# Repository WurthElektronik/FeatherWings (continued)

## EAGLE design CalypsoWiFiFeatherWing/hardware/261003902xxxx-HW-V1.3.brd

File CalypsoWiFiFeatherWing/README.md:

# Calypso Wi-Fi FeatherWing

## Introduction

The Würth Elektronik eiSos [Calypso Wi-Fi FeatherWing](https://www.we-online.de/katalog/en/CALYPSO_FeatherWing) is a development board that offers a secure 2.4 GHz Wi-Fi connectivity solution. It is fully compatible to the popular [Adafruit](https://www.adafruit.com/) [Feather line](https://www.adafruit.com/feather) of development boards and extends the Feathers with Wi-Fi connectivity.

The Calypso Wi-Fi FeatherWing consists of the [Calypso radio module](https://www.we-online.com/catalog/en/CALYPSO) that offers Wi-Fi connectivity based on **IEEE 802.11 b/g/n** with a fully featured TCP/IP stack. With out-of-the-box support to commonly used network applications like **SNTP**, **HTTP(S)**, **MQTT(S)**, Calypso offers easy and secure solutions to any **IoT application**.

It has an AT-style command interface on the standard UART and hence can be connected to any of the Feather microcontroller boards. The [Arduino](https://www.arduino.cc/) (C/C++) drivers and examples made available makes it easy to build a prototype to kick-start the application development.

This repository contains the [Eagle](https://www.autodesk.com/products/eagle/overview) design files for the Calypso Wi-Fi FeatherWing [PCB](hardware) as well as the [software](software) with quick start example.

For more information, please download the [Calypso Wi-Fi FeatherWing user manual](docs/CalypsoFeatherWing.pdf). Feel free to check our [YouTube channel](https://www.youtube.com/user/WuerthElektronik/videos) for video tutorials, hands-ons and webinars relating to our products.

## Hardware

### Description

The Calypso Wi-Fi FeatherWing was designed with rapid prototyping in mind. Being fully compatible with the Adafruit ecosystem, this FeatherWing gives the user the flexibility to choose the preferred host microcontroller. The inherent modularity of the ecosystem allows the FeatherWing to be easily integrated into any project.

### [Calypso Wi-Fi module](https://www.we-online.com/catalog/en/CALYPSO) [(2610011025000)](https://www.we-online.de/katalog/datasheet/2610011025000.pdf)

The Calypso Wi-Fi module is a compact Wi-Fi radio module based on IEEE 802.11 b/g/n with a fully featured TCP/IP stack. The edge castellated connections, smart antenna configuration and an easy-to-use AT-style command interface enable easy integration of the Calypso into any embedded application.

The module supports IPv4 as well as IPv6 and implements several commonly used network applications like SNTP, DHPv4, DHCPv6, mDNS, HTTP(S), MQTT(Secure) out-of the box. Advanced security features like up to 6 simultaneous secure sockets, secure boot, secure storage and secure OTA update provide a good basis for a secure end product.

Whether a serial cable replacement or low power IoT application with cloud connectivity, the Calypso Wi-Fi modules offers a robust and standard compliant wireless connectivity solution for low-power and low-medium throughput applications.

### Key features

Calypso offers the user to configure and exploit its rich features through an easy-to-use command interface over UART.

| Feature | Description |
| ------- | ----------- |
| Radio standards | IEEE 802.11 b/g/n station <br>IEEE 802.11 b/g Access point (for provisioning only)<br> Wi-Fi Direct client and group owner |
| Channels | 1-13 |
| Security | WEP, WPA/WPA2PSK, WPA2 Enterprise (802.1x) |
| Provisioning | In AP mode using the on-board HTTPS server |
| Network layer | IPv4, IPv6 |
| IP addresssing | Static, LLA, DHCPv4, DHCPv6 with DAD 
| Transport layer | TCP, UDP<br>SSLv3.0/TLSv1.0/TLSv1.1/TLSv1.2<br>Up to 15 simultaneous sockets of which 6 can be secure |
| Network applications | MQTT(Secure) client<br>HTTP(S) client<br>SNTP client<br>HTTP(S) server<br>mDNS, DNS-SD<br>DHCP server<br> Ping |
| Update | Secure OTA update with fall back mechanism |
| Security | Secure key storage<br>Trusted root-certificate catalog<br>Encrypted file system<br>Secure OTA<br>Software tamper detection<br>Cloning protection |
| Power management | 802.11 power save power modes <br>Lower power sleep mode with timed or pin wake-up |

### Pinouts 

#### Feather Connector
This is the standard set of connectors that is used across the Feather ecosystem. The table below describes the functions of each of the 28 pins as applicable to this FeatherWing.

| Pin number | Pin name | Function |
| ------- | ------- |----------------|
|    1          | <span style="text-decoration:overline">RST</span> | Not connected|
|    2          | 3V3| 3.3V power supply|
|    3          | AREF| Not connected|
|   4          | GND| Ground|
|    5          | A0| Not connected|
|    6          | A1| (Optional) Calypso APP_MODE_0 pin via JP3|
|    7          | A2| (Optional) Calypso APP_MODE_1 pin via JP3|
|    8          | A3| Not connected|
|    9          | A4| Not connected|
|    10         | A5| Not connected|
|    11         | SCK| Not connected|
|    12         | MOSI| Not connected|
|    13         | MISO| Not connected|
|    14         | U0RX| Calypso UTXD pin|
|    15         | U0TX| Calypso URXD Pin|
|    16         | NC| Not connected|

| Pin number | Pin name | Function |
| ------- | ------- |----------------|
|    17         | SDA| Not connected|
|    18         | SCL| Not connected|
|    19         | 5| Not connected|
|    20         | 6| (Optional) Calypso WAKE_UP pin via JP3|
|    21         | 9| Not connected|
|    22         | U1TX| Not connected|
|    23         | U1RX| Not connected|
|    24         | 12| (Optional) Switch S2 via JP3|
|    25         | 13| Not connected|
|    26         | 5V| Not connected|
|    27         | EN| Not connected|
|    28         | VBAT| Not connected|   

#### Jumper JP2
This jumper enables the user to start Calypso Wi-Fi module in different modes through the APP_MODE_0 and APP_MODE_1 pins. 

| Pin connection | Function  | Jumper set (Default) |
| ------- | ------- |----------------|
|    1,3	| APP_MODE_0 to HIGH |	No |
|    3,5	|APP_MODE_0 to LOW |	No |
|    2,4	| APP_MODE_1 to HIGH |	No |
|    4,6	|APP_MODE_1 to LOW |	No |

The table below briefly describes the different application modes of Calypso. Please refer to Section 5.2 of the Calypso [user manual](https://www.we-online.com/catalog/manual/2610011025000_Calypso%20261001102500x%20Manual_rev1.pdf) for further details. For normal operation in the standard AT-command mode, these jumpers do not need to be mounted as the lines are pulled down internally.

| APP_MODE_0 | APP_MODE_1  | Mode |
| ------- | ------- |----------------|
|    0	| 0  |	AT command normal mode |
|    0	|1 |	FOTA update mode |
|    1	| 0 |	Provisioning mode |
|    1	|1 |	AT command terminal mode |

#### Jumper JP3
This jumper allows the connection of Calypso pins APP_MODE_0, APP_MODE_1, WAKE_UP to the host microcontroller. Additionally, it allows the general purpose switch S2 to be connected to GPIO 12.

| Pin connection | Function  | Jumper set (Default) |
| ------- | ------- |----------------|
|    1,2|	S2 to GPIO12|	Yes|
|    3,4|	APP_MODE_0 to GPIOA1|	No|
|    5,6|	APP_MODE_1 to GPIOA2|	No|
|    7,8|	WAKE_UP to GPIO6|	No|

#### Push button S1
This push button is connected to the /RESET pin of the Calypso Wi-Fi module. Pressing this button resets the module.

#### Push button S2
S2 is a general purpose push button which is connected to GPIO 12 when a jumper is set between pins 1 and 2 of JP3. This switch can be used to trigger a specific action like switching the Calypso into provisioning mode.

### Schematics

### DISCLAIMER:
THE USE OF THE WÜRTH ELEKTRONIK EISOS DESIGN EXAMPLE / REFERENCE DESIGN IS ENTIRELY AT YOUR OWN RISK. IT IS YOUR SOLE RESPONSIBILITY TO IMPLEMENT THE DESIGN EXAMPLE / REFERENCE DESIGN WITH ALL TECHNICAL AND REGULATORY REQUIREMENTS IN YOUR APPLICATION. IT IS ALSO YOUR RESPONSIBILITY TO VERIFY THE FUNCTION AND PERFORMANCE OF YOUR DESIGN IN YOUR OWN PARTICULAR ENGINEERING AND PRODUCT ENVIRONMENT AND YOU ASSUME THE ENTIRE RISK OF DOING SO OR FAILING TO DO SO. THE WÜRTH ELEKTRONIK EISOS DESIGN EXAMPLE / REFERENCE DESIGN IS PROVIDED ON AN "AS IS" OR "AS AVAILABLE" BASIS, WITHOUT ANY WARRANTIES OF ANY KIND AND WÜRTH ELEKTRONIK EISOS DISCLAIMS ANY WARRANTIES EXPRESS OR IMPLIED, INCLUDING WITHOUT LIMITATION THE MERCHANTABILITY OR FITNESS FOR A PARTICULAR PURPOSE, USAGE OR THE NON-INFRINGEMENT OF THIRD PARTIES’ INTELLECTUAL PROPERTY RIGHTS. NO LICENSE IS GRANTED TO ANY INTELLECTUAL PROPERTY RIGHT BY WÜRTH ELEKTRONIK EISOS OR ANY THIRD PARY. UNDER NO CIRCUMSTANCES SHALL WÜRTH ELEKTRONIK EISOS BE LIABLE FOR DAMAGES INCURRED BY REASON OF OTHER SERVICES OR PRODUCTS RECEIVED THROUGH OR ADVERTISED IN CONNECTION WITH THE WÜRTH ELEKTRONIK EISOS SITE OR THE WÜRTH ELEKTRONIK EISOS DESIGN EXAMPLE / REFERENCE DESIGN. THE WÜRTH ELEKTRONIK EISOS DESIGN EXAMPLE / REFERENCE DESIGN IS SUBJECT TO CHANGE WITHOUT NOTICE.

## Software

A Calypso Wi-Fi FeatherWing quick start example can be found in the [software folder](software). Please check the [cloud connectivity folder](../Sensor2CloudConnectivity) for more examples for sensor to cloud solutions.

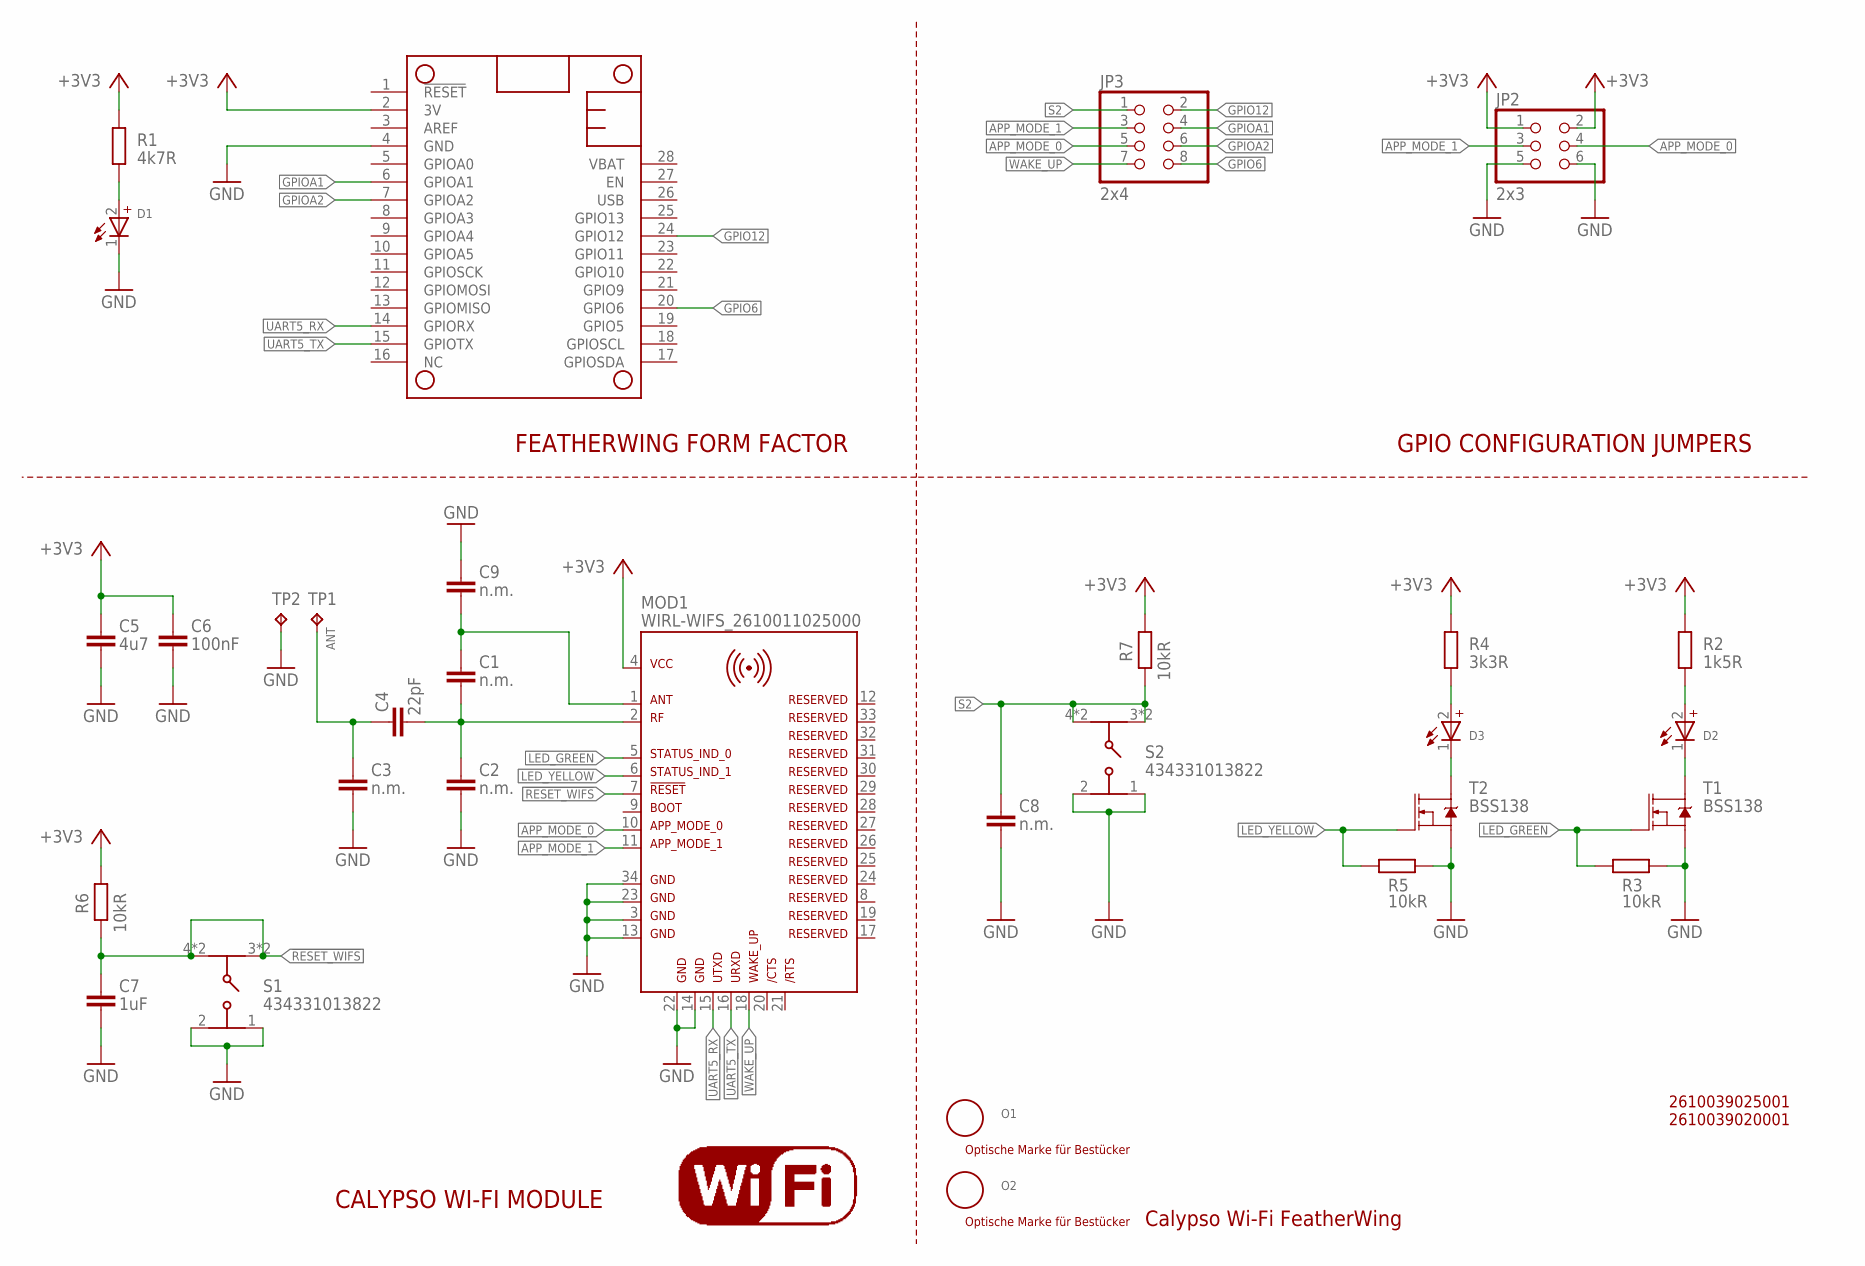
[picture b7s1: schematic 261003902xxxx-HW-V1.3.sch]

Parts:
C1, C8: n.m.; C0402_IPC
C2, C3, C9: n.m.; C0201_IPC
C4: 22pF; C0402_IPC
C5: 4u7; C0402_IPC
C6: 100nF; C0402_IPC
C7: 1uF; C0402_IPC
D1: RED; WL-SMSW_1204_A
D2: GREEN; WL-SMSW_1204_A
D3: YELLOW; WL-SMSW_1204_A
JP2: 2x3; 2X03
JP3: 2x4; 2X04
MOD1: WIRL-WIFS_2610011025000
MS1: header: 1 x 12 & 1 x 16; FEATHERWING_80MM
O1, O2: n.m.; OPTISCHE_MARKE
R1: 4k7R; R0402_IPC
R2: 1k5R; R0402_IPC
R3, R5, R6, R7: 10kR; R0402_IPC
R4: 3k3R; R0402_IPC
S1, S2: 434331013822
T1, T2: BSS138; SOT23-3
TP1, TP2: n.m.; D0.6
U$1: WIFI5MM; WIFI_5MM

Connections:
!RESET_WIFS: C7.1, MOD1.7, R6.1, S1.3, S1.4, S1.5 (3), S1.6 (4)
+3V3: C5.1, C6.1, JP2.1, JP2.2, MOD1.4, MS1.2 (3V), R1.2, R2.2, R4.2, R6.2, R7.2
ANT: C3.P$1 (1), C4.1, TP1.P$1
APP_MODE_0: JP2.4, JP3.5, MOD1.10
APP_MODE_1: JP2.3, JP3.3, MOD1.11
GND: C2.P$2 (2), C3.P$2 (2), C5.2, C6.2, C7.2, C8.2, C9.P$2 (2), D1.1 (-), JP2.5, JP2.6, MOD1.3, MOD1.13, MOD1.14, MOD1.22, MOD1.23, MOD1.34, MS1.4 (GND), R3.1, R5.1, S1.1, S1.2, S2.1, S2.2, T1.2 (S), T2.2 (S), TP2.P$1
GPIO6: JP3.8, MS1.20 (GPIO6)
GPIO12: JP3.2, MS1.24 (GPIO12)
GPIOA1: JP3.4, MS1.6 (GPIOA1)
GPIOA2: JP3.6, MS1.7 (GPIOA2)
LED_GREEN: MOD1.5, R3.2, T1.1 (G)
LED_YELLOW: MOD1.6, R5.2, T2.1 (G)
unnamed: D1.2 (+), R1.1
unnamed: C1.1, C2.P$1 (1), C4.2, MOD1.2
unnamed: C1.2, C9.P$1 (1), MOD1.1
unnamed: D2.2 (+), R2.1
unnamed: D2.1 (-), T1.3 (D)
unnamed: D3.2 (+), R4.1
unnamed: D3.1 (-), T2.3 (D)
S2: C8.1, JP3.1, R7.1, S2.3, S2.4, S2.5 (3), S2.6 (4)
UART5_RX: MOD1.15, MS1.14 (GPIORX)
UART5_TX: MOD1.16, MS1.15 (GPIOTX)
WAKE_UP: JP3.7, MOD1.18

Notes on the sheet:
Calypso Wi-Fi FeatherWing
FEATHERWING FORM FACTOR
CALYPSO WI-FI MODULE
GPIO CONFIGURATION JUMPERS
2610039025001 2610039020001

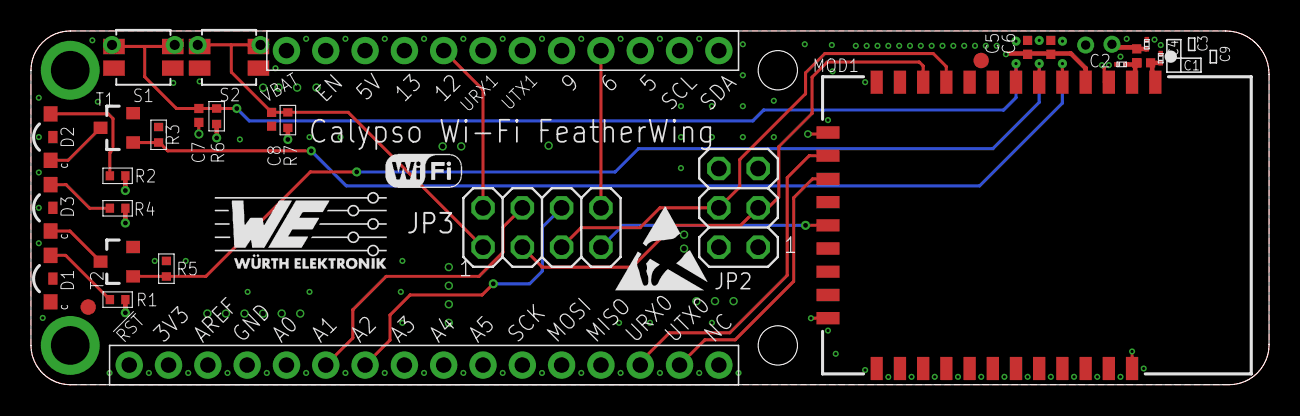
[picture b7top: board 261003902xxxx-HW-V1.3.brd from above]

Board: 4 copper layers, 80.0 x 22.9 mm, 35 parts (1 on the bottom side), 23 nets.

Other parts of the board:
U$2: WE-LOGO-5MM_TNAME
U$4: FEATHER_12MM
U$5: ESD_6MM

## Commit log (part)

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2020-11-02 Added readme files
2020-11-02 Readme files for each featherwing
2020-11-02 * Assets created for the WE specific style and logos * MagIC Power FeatherFing folder created
2020-11-02 path made relativefor we logo in magic
2020-11-02 Magic board front and back views addedto the assets
2020-11-02 Update README.md
    html image style added
2020-11-02 pipelined size removed for images in md file
2020-11-02 missing folder name removed
2020-11-02 Quickstart example for Thyone
2020-11-02 Quick start example for calypso FeatherWing
2020-11-02 Calypso default README created and picture the marketing added. WE Logo added to som md files
2020-11-02 inital connection image name corrected
2020-11-02 we logo added to the calypso readme mds
2020-11-03 IoT hub connection documentation changed to describe IoTHub creation
2020-11-03 Updated Thyone to print RSSI and US get before write
2020-11-03 logo fixed in main readme
2020-11-03 rewriting readme.md
2020-11-04 SQL database creation description started for Calypso in Azure
2020-11-04 Added Azure connection implementation
2020-11-04 Sensor data over Calypso to Azure
2020-11-06 Missing backtick added
2020-11-06 some spelling corrected
2020-11-06 link to default root
2020-11-06 Thyone software documentation in readme.md
2020-11-06 Thyone picture added
2020-11-09 SQL connection added to Calypso .md
2020-11-10 excel connection for Calypso Thyone-I minor changes
2020-11-10 tips and notes added
2020-11-10 Tip and Note box type changed
2020-11-10 Excel database choise and firewall description added to Calypso Azure description.
2020-11-10 Azure visualisation in excel for Calypso
2020-11-10 WE Logo replaced with the smaller one
2020-11-11 feather logo added
2020-11-11 Stacked image changed
2020-11-11 separated images added for main md
2020-11-11 test bold and link in table with images
2020-11-11 ul/li combination used instead of br
2020-11-11 table without header
2020-11-11 table with header
2020-11-11 Added Ca;ypso/sensor combo readme.md
2020-11-11 SSID and PW set to neutral
2020-11-11 Magic completly moved to hardware repository, since there are no software examples for this FeatherWing
2020-11-11 Default Calypso MQTT code added to the README.md
2020-11-11 Added license terms
2020-11-12 Calypso FeatherWing renamed to Calypso WiFi FeatherWing
2020-11-12 Calypro folder renamed
2020-11-12 Calypso folder name change implemented in the files
2020-11-12 Calypso images for code and VS code extensions added
2020-11-12 Cloud link changed to cloud examples and not tho the specific one
2020-11-12 Updated text in the readme from the latest documentation
2020-11-12 Code language defined description for the database creation added to the CalypsoSensorCombo
2020-11-13 small cosmeti changes
2020-11-13 IoTHub names changed to neutral in main.cpp files
2020-11-17 Update README.md
    some minor spelling corrections
2020-11-17 Update README.md
    highlighted "build" and "upload" from PlatformIO description
2020-11-17 Update README.md
    corrected couple of misspells until "IoTHub 5"
2020-11-18 Bugfix -SNTP settings fail
2020-11-18 Added reconnect in case of wifi error
2020-11-20 Heading changed
2020-11-20 SME comments for Azure descriptions incorporated
2020-11-20 Device (thing) creation in IoT Core for AWS added
2020-11-24 AWS implementation
2020-11-24 Create and register policy for the AWS IoT thing
2020-11-24 Create AWS IoT Core rule added to AWS docu
2020-11-24 Visualise data using AWS QuickSight
2020-11-24 Create Lambda functions added
2020-11-25 Updates to the quick start example description
2020-11-25 Minor spelling corrected
2020-11-26 Restructuring and combination
2020-11-26 Updated workspaces and links in projects
2020-11-26 Testing links
2020-11-26 Readme CalypsoFW done
2020-11-26 Added readme to common folder
2020-11-26 Update - SensorFW readme
2020-11-26 Update Thyone readme
2020-11-26 Corrected links
2020-11-26 Fixed cloud workspace
2020-11-26 Document update
2020-11-26 Web App visualisation added to the sensor2cloud
2020-11-26 spelling corrected
2020-11-27 Data extracted and charts added for humidity and acceleration
2020-11-27 all data from all sensors added to the addData method, but only the most important displayed.
2020-11-28 Unnecessary data removed
2020-11-30 FeatherWing images chaged on the first page and links to SparkFun and WE added
2020-11-30 AWS QuickSight image added to the AWS readme
2020-11-30 Images position fixed
2020-11-30 AWS minor changes in the documentation
2020-11-30 Empty spaces
2020-11-30 AWS small text corrections
2020-12-01 Minor text changes
2020-12-01 Link and minor formating changes in aws part
2021-01-13 Sensor data visualisation immage added and AWS lambda code changed
2021-01-22 correction of the quick start point 6.
2021-01-22 Sensor Workspace used for the quick start guide.
2021-01-25 Bootstrap.sh and AWS manifest.json file for the S3 bucket removed from the reposiuory
2021-01-29 Added subscribe function to calypso
2021-02-02 SAS token generation described
2021-02-02 SAS token images moved with spaces
2021-02-02 Spaces added for the HTML picture position correction
2021-02-03 Updated quick start guide
2021-02-03 Git link added to the software quicksart guide
2021-02-08 JeRu changes incorporated
2021-02-08 Spelling checked and images moved to a new line to avoid blanks. Hyperchage word replaced with supercharge
2021-02-09 Update README.md
    some minor spelling corrected
2021-02-10 Improved documentation.
2021-02-23 Bug fix + documentation update
2021-02-24 Updated hadware files for the sensorFeatherWing
2021-02-24 Improved UART timing for Calypso and Thyone FeatherWing
2021-05-18 fix for: CVE-2021-23337 -> lodash update to version >= 4.17.21 CVE-2021-23362 -> hosted-git-info update to version >= 2.8.9
2021-06-16 Bump ws
    Bumps [ws](https://github.com/websockets/ws) from 7.1.2 to 7.4.6.
    - [Release notes](https://github.com/websockets/ws/releases)
    - [Commits](https://github.com/websockets/ws/compare/7.1.2...7.4.6)
    ---
    updated-dependencies:
    - dependency-name: ws
2021-06-16 Bump glob-parent
    Bumps [glob-parent](https://github.com/gulpjs/glob-parent) from 5.1.1 to 5.1.2.
    - [Release notes](https://github.com/gulpjs/glob-parent/releases)
    - [Changelog](https://github.com/gulpjs/glob-parent/blob/main/CHANGELOG.md)
    - [Commits](https://github.com/gulpjs/glob-parent/compare/v5.1.1...v5.1.2)
    ---
    updated-dependencies:
2022-02-13 Bump ajv
    Bumps [ajv](https://github.com/ajv-validator/ajv) from 6.12.0 to 6.12.6.
    - [Release notes](https://github.com/ajv-validator/ajv/releases)
    - [Commits](https://github.com/ajv-validator/ajv/compare/v6.12.0...v6.12.6)
    ---
    updated-dependencies:
    - dependency-name: ajv
2022-02-21 Updated libraries and added new example
2022-03-28 Bump minimist
    Bumps [minimist](https://github.com/substack/minimist) from 1.2.5 to 1.2.6.
    - [Release notes](https://github.com/substack/minimist/releases)
    - [Commits](https://github.com/substack/minimist/compare/1.2.5...1.2.6)
    ---
    updated-dependencies:
    - dependency-name: minimist
2022-09-23 Bump ansi-regex
    Bumps [ansi-regex](https://github.com/chalk/ansi-regex) from 4.1.0 to 4.1.1.
    - [Release notes](https://github.com/chalk/ansi-regex/releases)
    - [Commits](https://github.com/chalk/ansi-regex/compare/v4.1.0...v4.1.1)
    ---
    updated-dependencies:
    - dependency-name: ansi-regex
2022-09-23 Added the Proteus-III FeatherWing with an example
2022-11-10 Bump minimatch
    Bumps [minimatch](https://github.com/isaacs/minimatch) from 3.0.4 to 3.1.2.
    - [Release notes](https://github.com/isaacs/minimatch/releases)
    - [Commits](https://github.com/isaacs/minimatch/compare/v3.0.4...v3.1.2)
    ---
    updated-dependencies:
    - dependency-name: minimatch
2022-12-06 Bump qs and express
    Bumps [qs](https://github.com/ljharb/qs) to 6.11.0 and updates ancestor dependency [express](https://github.com/expressjs/express). These dependencies need to be updated together.
    Updates `qs` from 6.9.2 to 6.11.0
    - [Release notes](https://github.com/ljharb/qs/releases)
    - [Changelog](https://github.com/ljharb/qs/blob/main/CHANGELOG.md)
    - [Commits](https://github.com/ljharb/qs/compare/v6.9.2...v6.11.0)
    Updates `express` from 4.17.1 to 4.18.2
2023-02-06 information clarified & updated
2023-03-03 Bump qs
    Bumps [qs](https://github.com/ljharb/qs) from 6.9.2 to 6.9.7.
    - [Release notes](https://github.com/ljharb/qs/releases)
    - [Changelog](https://github.com/ljharb/qs/blob/main/CHANGELOG.md)
    - [Commits](https://github.com/ljharb/qs/compare/v6.9.2...v6.9.7)
    ---
    updated-dependencies:
2023-03-03 Update connection to Azure IoT
2023-07-09 Bump tough-cookie and @azure/core-http
    Bumps [tough-cookie](https://github.com/salesforce/tough-cookie) and [@azure/core-http](https://github.com/Azure/azure-sdk-for-js). These dependencies needed to be updated together.
    Updates `tough-cookie` from 3.0.1 to 4.1.3
    - [Release notes](https://github.com/salesforce/tough-cookie/releases)
    - [Changelog](https://github.com/salesforce/tough-cookie/blob/master/CHANGELOG.md)
    - [Commits](https://github.com/salesforce/tough-cookie/commits/v4.1.3)
    Updates `@azure/core-http` from 1.0.4 to 1.2.6
2023-11-02 Bump word-wrap
    Bumps [word-wrap](https://github.com/jonschlinkert/word-wrap) from 1.2.3 to 1.2.5.
    - [Release notes](https://github.com/jonschlinkert/word-wrap/releases)
    - [Commits](https://github.com/jonschlinkert/word-wrap/compare/1.2.3...1.2.5)
    ---
    updated-dependencies:
    - dependency-name: word-wrap
2023-11-02 Bump debug
    Bumps and [debug](https://github.com/debug-js/debug). These dependencies needed to be updated together.
    Updates `debug` from 4.1.1 to 4.3.4
    - [Release notes](https://github.com/debug-js/debug/releases)
    - [Commits](https://github.com/debug-js/debug/compare/4.1.1...4.3.4)
    Updates `debug` from 3.2.6 to 4.3.4
    - [Release notes](https://github.com/debug-js/debug/releases)
2023-11-03 Restructured SDK and added new FeatherWings
2024-01-11 Bump follow-redirects
    Bumps [follow-redirects](https://github.com/follow-redirects/follow-redirects) from 1.15.2 to 1.15.4.
    - [Release notes](https://github.com/follow-redirects/follow-redirects/releases)
    - [Commits](https://github.com/follow-redirects/follow-redirects/compare/v1.15.2...v1.15.4)
    ---
    updated-dependencies:
    - dependency-name: follow-redirects
2024-03-06 added Hardware & Schematics related disclaimer to all FeatherWings.
2024-03-14 - ProteusIII, ThyoneI: fix UserSettings wait for confirm - Sensor2BLE: check for minimum version of ProteusIII v1.4.0 instead of only v1.4.0
2024-03-28 Bump express
    Bumps [express](https://github.com/expressjs/express) from 4.17.3 to 4.19.2.
    - [Release notes](https://github.com/expressjs/express/releases)
    - [Changelog](https://github.com/expressjs/express/blob/master/History.md)
    - [Commits](https://github.com/expressjs/express/compare/4.17.3...4.19.2)
    ---
    updated-dependencies:
2024-06-17 ICLEDFeatheWing added
2024-07-03 AdrasteaI: ATMQTT: Fix add \r\n to aws iot commands
2024-07-15 Add ICLEDFeatherWing
2024-07-15 Delete ICLEDFeatherWing/software/lib/WE_LED_Featherwing/src directory
    Deleted software version 1,0
2024-07-15 Included ICLEDFeatherWing BOM - Hardware v1.0
2024-08-07 Updated User Manual for the ICLED Featherwing with CI
2024-09-11 Added User Manual v1.1
2025-04-17 Release v2.2.0
2025-06-03 Bump tar-fs
    Bumps [tar-fs](https://github.com/mafintosh/tar-fs) from 2.1.1 to 2.1.3.
    - [Commits](https://github.com/mafintosh/tar-fs/commits)
    ---
    updated-dependencies:
    - dependency-name: tar-fs
    dependency-version: 2.1.3
